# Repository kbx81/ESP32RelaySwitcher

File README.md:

# kbx's 8-channel ESP32-Powered Relay + I/O Board

## What?

A simple ESP32-based board with eight relays for switching various loads
 as well as terminals for eight external/panel-mounted buttons. Also includes
 a terminal strip for connecting one-wire temperature sensor probes. Designed
 to operate with a 24 VAC power supply.

## Why?

A friend asked me to.

## How?

The schematic and PCB were drawn in [KiCAD](https://www.kicad.org); all project files are contained within this repo.

## Look

## Legal stuff and License

The circuit schematics and PCB found here are licensed under the
 [Creative Commons Attribution-ShareAlike 4.0 International License](http://creativecommons.org/licenses/by-sa/4.0/).

_Happy building!_

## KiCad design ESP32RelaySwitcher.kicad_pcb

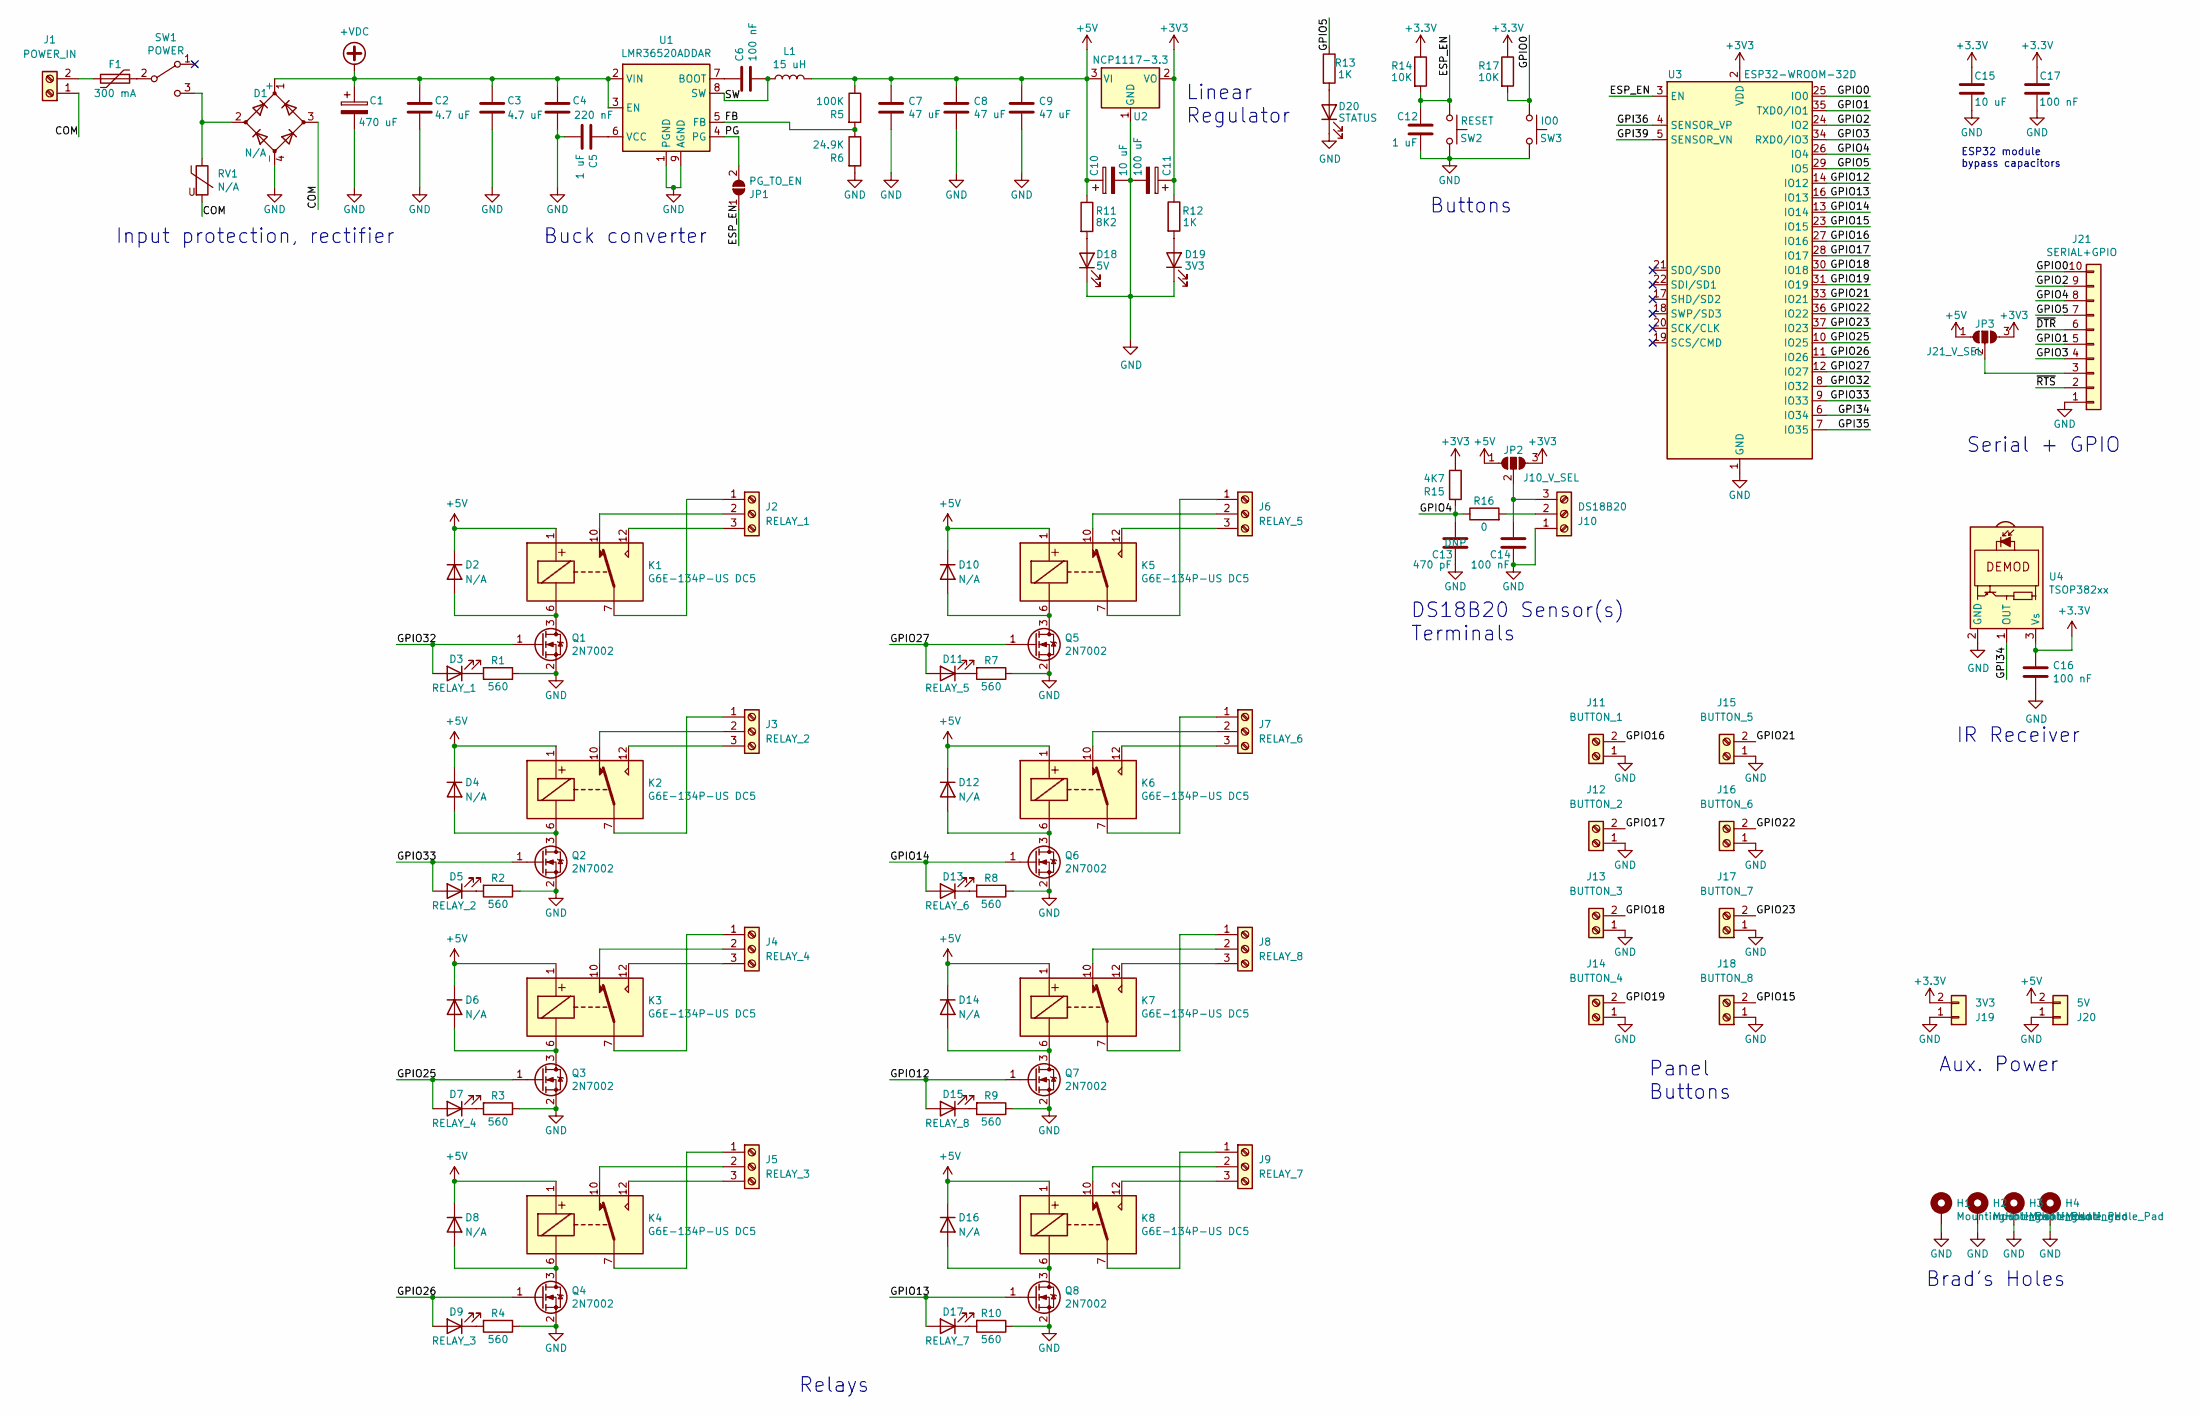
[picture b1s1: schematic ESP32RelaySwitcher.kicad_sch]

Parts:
C1: 470 uF; CP_Elec_16x17.5; MPN1 EEV-FK1H471M
C2, C3: 4.7 uF; C_0805_2012Metric; MPN1 C2012X5R1H475K125AB
C4: 220 nF; C_0805_2012Metric; MPN1 C2012X5R1H224K125AA
C5: 1 uF; C_0805_2012Metric; MPN1 C0805C105K4RACTU
C6: 100 nF; C_0805_2012Metric; MPN1 CC0805KRX7R7BB104
C7, C8, C9: 47 uF; C_1210_3225Metric; MPN1 GRM32ER61C476KE15L
C10: 10 uF; CP_Elec_4x5.8; Part AFK106M25B12T-F
C11: 100 uF; CP_Elec_5x5.4; Part UWR1A101MCL1GB
C12: 1 uF; C_0805_2012Metric; MPN1 C2012X5R1E105M125AA
C13: 470 pF; C_0805_2012Metric; Part CC0805KRX7R8BB471
C14, C16, C17: 100 nF; C_0805_2012Metric; Part CC0805KRX7R7BB104
C15: 10 uF; C_0805_2012Metric; MPN1 GRM21BC81C106ME15L
D1: N/A; Diode_Bridge_Bourns_CD-MBL2xxS; MPN1 CD-MBL206SL
D2, D4, D6, D8, D10, D12, D14, D16: N/A; D_SOD-123; MPN1 1N4148W
D3: RELAY_1; LED_0805_2012Metric; MPN1 APTL3216CGCK
D5: RELAY_2; LED_0805_2012Metric; MPN1 APTL3216CGCK
D7: RELAY_4; LED_0805_2012Metric; MPN1 APTL3216CGCK
D9: RELAY_3; LED_0805_2012Metric; MPN1 APTL3216CGCK
D11: RELAY_5; LED_0805_2012Metric; MPN1 APTL3216CGCK
D13: RELAY_6; LED_0805_2012Metric; MPN1 APTL3216CGCK
D15: RELAY_8; LED_0805_2012Metric; MPN1 APTL3216CGCK
D17: RELAY_7; LED_0805_2012Metric; MPN1 APTL3216CGCK
D18: 5V; LED_0805_2012Metric; MPN1 597-6901-607F
D19: 3V3; LED_0805_2012Metric; MPN1 597-6901-607F
D20: STATUS; LED_0805_2012Metric; MPN1 597-6901-607F
F1: 300 mA; Fuse_2920_7451Metric; MPN1 2920L030DR
H1, H2, H3, H4: MountingHole_Pad; MountingHole_3.2mm_M3_Pad_Via
J1: POWER_IN; TerminalBlock_Phoenix_PT-1,5-2-3.5-H_1x02_P3.50mm_Horizontal
J2: RELAY_1; TerminalBlock_Phoenix_PT-1,5-3-3.5-H_1x03_P3.50mm_Horizontal
J3: RELAY_2; TerminalBlock_Phoenix_PT-1,5-3-3.5-H_1x03_P3.50mm_Horizontal
J4: RELAY_4; TerminalBlock_Phoenix_PT-1,5-3-3.5-H_1x03_P3.50mm_Horizontal
J5: RELAY_3; TerminalBlock_Phoenix_PT-1,5-3-3.5-H_1x03_P3.50mm_Horizontal
J6: RELAY_5; TerminalBlock_Phoenix_PT-1,5-3-3.5-H_1x03_P3.50mm_Horizontal
J7: RELAY_6; TerminalBlock_Phoenix_PT-1,5-3-3.5-H_1x03_P3.50mm_Horizontal
J8: RELAY_8; TerminalBlock_Phoenix_PT-1,5-3-3.5-H_1x03_P3.50mm_Horizontal
J9: RELAY_7; TerminalBlock_Phoenix_PT-1,5-3-3.5-H_1x03_P3.50mm_Horizontal
J10: DS18B20; TerminalBlock_Phoenix_PT-1,5-3-3.5-H_1x03_P3.50mm_Horizontal
J11: BUTTON_1; TerminalBlock_Phoenix_PT-1,5-2-3.5-H_1x02_P3.50mm_Horizontal
J12: BUTTON_2; TerminalBlock_Phoenix_PT-1,5-2-3.5-H_1x02_P3.50mm_Horizontal
J13: BUTTON_3; TerminalBlock_Phoenix_PT-1,5-2-3.5-H_1x02_P3.50mm_Horizontal
J14: BUTTON_4; TerminalBlock_Phoenix_PT-1,5-2-3.5-H_1x02_P3.50mm_Horizontal
J15: BUTTON_5; TerminalBlock_Phoenix_PT-1,5-2-3.5-H_1x02_P3.50mm_Horizontal
J16: BUTTON_6; TerminalBlock_Phoenix_PT-1,5-2-3.5-H_1x02_P3.50mm_Horizontal
J17: BUTTON_7; TerminalBlock_Phoenix_PT-1,5-2-3.5-H_1x02_P3.50mm_Horizontal
J18: BUTTON_8; TerminalBlock_Phoenix_PT-1,5-2-3.5-H_1x02_P3.50mm_Horizontal
J19: 3V3; PinSocket_1x02_P2.54mm_Vertical
J20: 5V; PinSocket_1x02_P2.54mm_Vertical
J21: SERIAL+GPIO; PinSocket_1x10_P2.54mm_Vertical
JP1: PG_TO_EN; SolderJumper-2_P1.3mm_Open_RoundedPad1.0x1.5mm; MPN1 N/A
JP2: J10_V_SEL; SolderJumper-3_P1.3mm_Open_RoundedPad1.0x1.5mm; MPN1 N/A
JP3: J21_V_SEL; SolderJumper-3_P1.3mm_Open_RoundedPad1.0x1.5mm; MPN1 N/A
K1, K2, K3, K4, K5, K6, K7, K8: G6E-134P-US DC5; Relay_SPDT_Omron_G6E; MPN1 G6E-134P-US DC5
L1: 15 uH; L_Wuerth_WE-PD-Typ-LS; MPN1 7447709150
Q1, Q2, Q3, Q4, Q5, Q6, Q7, Q8: 2N7002; SOT-23; MPN1 2N7002
R1, R2, R3, R4, R7, R8, R9, R10: 560; R_0805_2012Metric; MPN1 RT0805FRE07560RL
R5: 100K; R_0805_2012Metric; MPN1 RC0805FR-07100KL
R6: 24.9K; R_0805_2012Metric; MPN1 RT0805FRE0724K9L
R11: 8K2; R_0805_2012Metric; MPN1 RT0805FRE078K2L
R12, R13: 1K; R_0805_2012Metric; MPN1 RC0805FR-071KL
R14, R17: 10K; R_0805_2012Metric; MPN1 RC0805FR-0710KL
R15: 4K7; R_0805_2012Metric; Part RC0805FR-074K7L
R16: 0; R_0805_2012Metric; Part RC0805FR-070RL
RV1: N/A; RV_Disc_D7mm_W4mm_P5mm; MPN1 B72205S0400K101
SW1: POWER; SW_Push_1P2T_Vertical_E-Switch_800UDP8P1A1M6; MPN1 48BFSP1M6QT
SW2: RESET; SW_Tactile_SPST_Angled_PTS645Vx58-2LFS; MPN1 PTS645VK582LFS
SW3: IO0; SW_Tactile_SPST_Angled_PTS645Vx58-2LFS; MPN1 PTS645VK582LFS
U1: LMR36520ADDAR; Texas_HSOP-8-1EP_3.9x4.9mm_P1.27mm_ThermalVias; MPN1 LMR36520ADDAR
U2: NCP1117-3.3; TO-252-2
U3: ESP32-WROOM-32D; ESP32-WROOM-32; MPN1 ESP32-WROOM-32D
U4: TSOP382xx; Vishay_MINICAST-3Pin

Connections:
+5V: C7.1, C8.1, C9.1, C10.1, D2.1 (K), D4.1 (K), D6.1 (K), D8.1 (K), D10.1 (K), D12.1 (K), D14.1 (K), D16.1 (K), J20.2, JP2.1 (A), JP3.1 (A), K1.1, K2.1, K3.1, K4.1, K5.1, K6.1, K7.1, K8.1, L1.2, R5.1, R11.1, U2.3 (VI)
+VDC: C1.1, C2.1, C3.1, C4.1, D1.1 (+), U1.2 (VIN), U1.3 (EN)
/COM: D1.3, J1.1, RV1.2
/ESP_EN: C12.1, JP1.1 (A), R14.2, SW2.1, U3.3 (EN)
/FB: R5.2, R6.1, U1.5 (FB)
/GPI34: U3.6 (IO34), U4.1 (OUT)
/GPI35: U3.7 (IO35)
/GPI36: U3.4 (SENSOR_VP)
/GPI39: U3.5 (SENSOR_VN)
/GPIO0: J21.10, R17.2, SW3.1, U3.25 (IO0)
/GPIO1: J21.5, U3.35 (TXD0/IO1)
/GPIO2: J21.9, U3.24 (IO2)
/GPIO3: J21.4, U3.34 (RXD0/IO3)
/GPIO4: C13.1, J21.8, R15.2, R16.1, U3.26 (IO4)
/GPIO5: J21.7, R13.1, U3.29 (IO5)
/GPIO12: D15.2 (A), Q7.1 (G), U3.14 (IO12)
/GPIO13: D17.2 (A), Q8.1 (G), U3.16 (IO13)
/GPIO14: D13.2 (A), Q6.1 (G), U3.13 (IO14)
/GPIO15: J18.2, U3.23 (IO15)
/GPIO16: J11.2, U3.27 (IO16)
/GPIO17: J12.2, U3.28 (IO17)
/GPIO18: J13.2, U3.30 (IO18)
/GPIO19: J14.2, U3.31 (IO19)
/GPIO21: J15.2, U3.33 (IO21)
/GPIO22: J16.2, U3.36 (IO22)
/GPIO23: J17.2, U3.37 (IO23)
/GPIO25: D7.2 (A), Q3.1 (G), U3.10 (IO25)
/GPIO26: D9.2 (A), Q4.1 (G), U3.11 (IO26)
/GPIO27: D11.2 (A), Q5.1 (G), U3.12 (IO27)
/GPIO32: D3.2 (A), Q1.1 (G), U3.8 (IO32)
/GPIO33: D5.2 (A), Q2.1 (G), U3.9 (IO33)
/PG: JP1.2 (B), U1.4 (PG)
/SW: C6.2, L1.1, U1.8 (SW)
/~DTR: J21.6
/~RTS: J21.2
GND: C1.2, C2.2, C3.2, C4.2, C5.2, C7.2, C8.2, C9.2, C10.2, C11.2, C12.2, C13.2, C14.2, C15.2, C16.2, C17.2, D1.4 (-), D18.1 (K), D19.1 (K), D20.1 (K), H1.1, H2.1, H3.1, H4.1, J10.1, J11.1, J12.1, J13.1, J14.1, J15.1, J16.1, J17.1, J18.1, J19.1, J20.1, J21.1, Q1.2 (S), Q2.2 (S), Q3.2 (S), Q4.2 (S), Q5.2 (S), Q6.2 (S), Q7.2 (S), Q8.2 (S), R1.1, R2.1, R3.1, R4.1, R6.2, R7.1, R8.1, R9.1, R10.1, SW2.2, SW3.2, U1.1 (PGND), U1.9 (AGND), U2.1 (GND), U3.1 (GND), U3.15 (GND), U3.38 (GND), U3.39 (GND), U4.2 (GND)
unnamed: C5.1, U1.6 (VCC)
unnamed: C6.1, U1.7 (BOOT)
unnamed: C14.1, J10.3, JP2.2 (C)
unnamed: D1.2, RV1.1, SW1.3 (C)
unnamed: D2.2 (A), K1.6, Q1.3 (D)
unnamed: D3.1 (K), R1.2
unnamed: D4.2 (A), K2.6, Q2.3 (D)
unnamed: D5.1 (K), R2.2
unnamed: D6.2 (A), K3.6, Q3.3 (D)
unnamed: D7.1 (K), R3.2
unnamed: D8.2 (A), K4.6, Q4.3 (D)
unnamed: D9.1 (K), R4.2
unnamed: D10.2 (A), K5.6, Q5.3 (D)
unnamed: D11.1 (K), R7.2
unnamed: D12.2 (A), K6.6, Q6.3 (D)
unnamed: D13.1 (K), R8.2
unnamed: D14.2 (A), K7.6, Q7.3 (D)
unnamed: D15.1 (K), R9.2
unnamed: D16.2 (A), K8.6, Q8.3 (D)
unnamed: D17.1 (K), R10.2
unnamed: D18.2 (A), R11.2
unnamed: D19.2 (A), R12.2
unnamed: D20.2 (A), R13.2
unnamed: F1.1, SW1.2 (B)
unnamed: F1.2, J1.2
unnamed: J2.1, K1.7
unnamed: J2.2, K1.10
unnamed: J2.3, K1.12
unnamed: J3.1, K2.7
unnamed: J3.2, K2.10
unnamed: J3.3, K2.12
unnamed: J4.1, K3.7
unnamed: J4.2, K3.10
unnamed: J4.3, K3.12
unnamed: J5.1, K4.7
unnamed: J5.2, K4.10
unnamed: J5.3, K4.12
unnamed: J6.1, K5.7
unnamed: J6.2, K5.10
unnamed: J6.3, K5.12
unnamed: J7.1, K6.7
unnamed: J7.2, K6.10
unnamed: J7.3, K6.12
unnamed: J8.1, K7.7
unnamed: J8.2, K7.10
unnamed: J8.3, K7.12
unnamed: J9.1, K8.7
unnamed: J9.2, K8.10
unnamed: J9.3, K8.12
unnamed: J10.2, R16.2
unnamed: J21.3, JP3.2 (C)

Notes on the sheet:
Buttons
Buck converter
Aux. Power
DS18B20 Sensor(s) Terminals
ESP32 module bypass capacitors
Linear Regulator
Input protection, rectifier
Panel Buttons
Relays
IR Receiver
Brad's Holes
Serial + GPIO

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
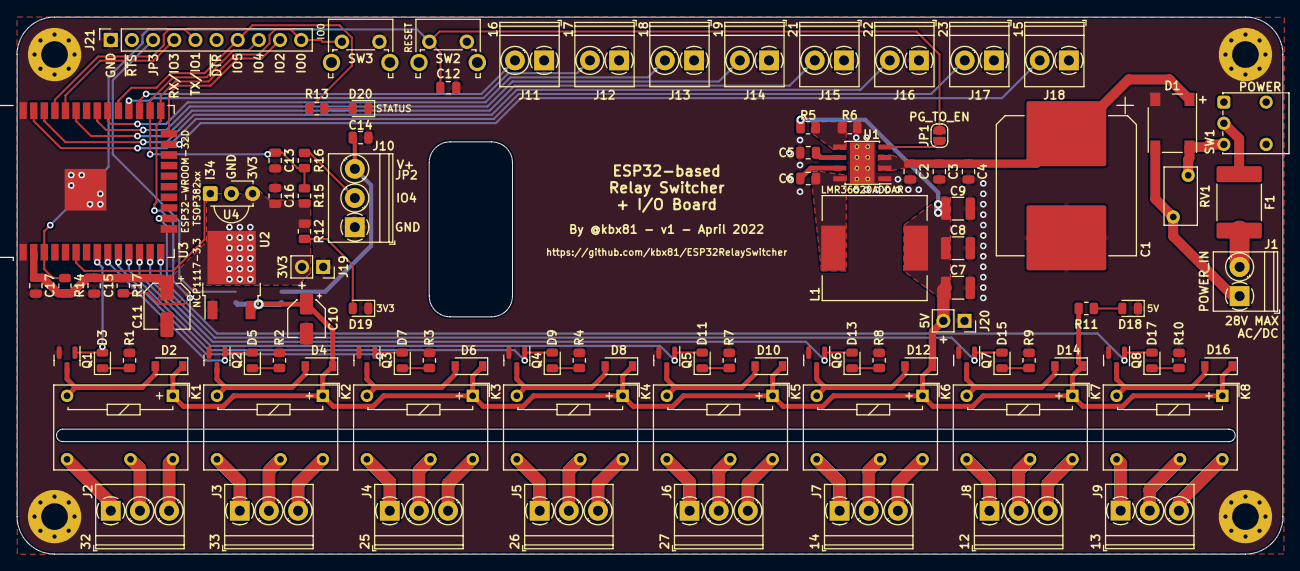
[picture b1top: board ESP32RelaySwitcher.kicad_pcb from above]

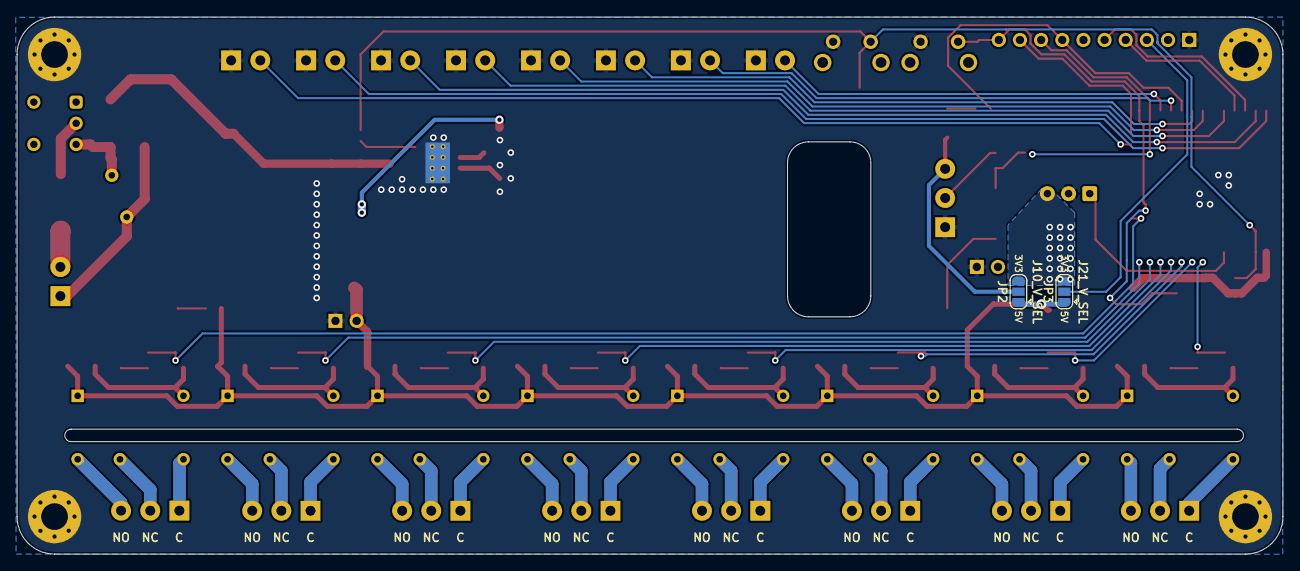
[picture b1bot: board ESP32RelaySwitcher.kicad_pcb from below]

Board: 2 copper layers, 152.0 x 64.5 mm, 108 parts (2 on the bottom side), 83 nets.

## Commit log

2022-04-09 Use parts I can actually get...
2022-04-09 Add docs and board render image
2022-04-09 Finishing
2023-04-25 Add BoM, update images
